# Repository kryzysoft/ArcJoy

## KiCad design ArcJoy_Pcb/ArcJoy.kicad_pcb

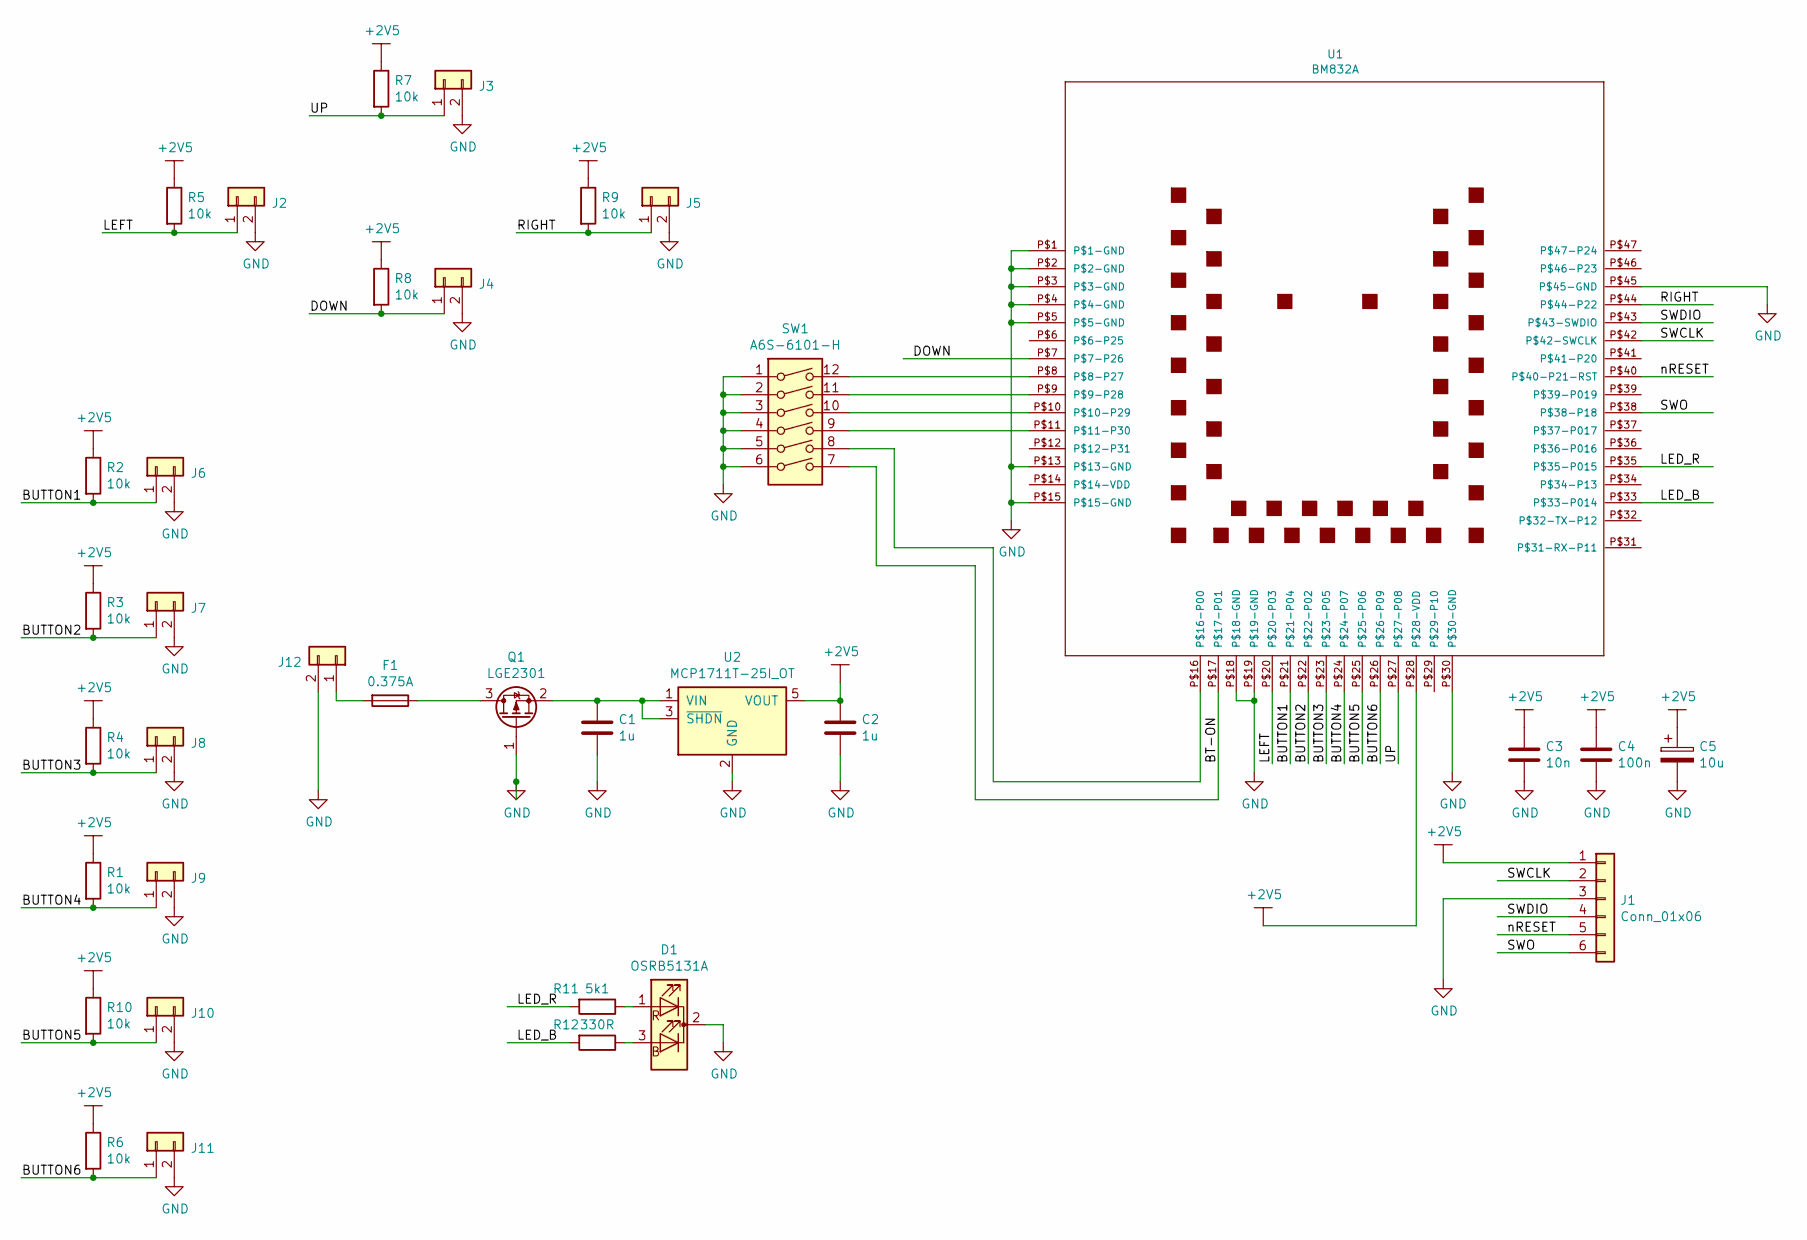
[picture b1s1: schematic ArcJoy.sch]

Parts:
C1, C2: 1u; C_1206_3216Metric
C3: 10n; C_1206_3216Metric
C4: 100n; C_1206_3216Metric
C5: 10u; CP_EIA-6032-28_Kemet-C
D1: OSRB5131A; LED_D5.0mm-3
F1: 0.375A; Fuse_2.6x6.1
J1: Conn_01x06; PinHeader_1x06_P2.54mm_Vertical
J2, J3, J4, J5: Conn_01x02; PinHeader_1x02_P2.54mm_Vertical
J6, J7, J8, J9, J10, J11, J12: Conn_01x02; NINIGI_TB-3.5-P-2P_BL
Q1: LGE2301; SOT-23
R1, R2, R3, R4, R5, R6, R7, R8, R9, R10: 10k; R_1206_3216Metric
R11: 5k1_1206_1%; R_1206_3216Metric
R12: 330R_1206_1%; R_1206_3216Metric
SW1: A6S-6101-H; SW_DIP_SPSTx06_Slide_Omron_A6S-610x_W8.9mm_P2.54mm
U1: BM832A; BM832-1-BM832
U2: MCP1711T-25I_OT; SOT-23-5

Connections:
+2V5: C2.1, C3.1, C4.1, C5.1, J1.1, R1.1, R2.1, R3.1, R4.1, R5.1, R6.1, R7.1, R8.1, R9.1, R10.1, U1.P$28 (P$28-VDD), U2.5 (VOUT)
/BT-ON: SW1.7, U1.P$17 (P$17-P01)
/BUTTON1: J6.1, R2.2, U1.P$21 (P$21-P04)
/BUTTON2: J7.1, R3.2, U1.P$22 (P$22-P02)
/BUTTON3: J8.1, R4.2, U1.P$23 (P$23-P05)
/BUTTON4: J9.1, R1.2, U1.P$24 (P$24-P07)
/BUTTON5: J10.1, R10.2, U1.P$25 (P$25-P06)
/BUTTON6: J11.1, R6.2, U1.P$26 (P$26-P09)
/DOWN: J4.1, R8.2, U1.P$7 (P$7-P26)
/LED_B: R12.2, U1.P$33 (P$33-P014)
/LED_R: R11.2, U1.P$35 (P$35-P015)
/LEFT: J2.1, R5.2, U1.P$20 (P$20-P03)
/RIGHT: J5.1, R9.2, U1.P$44 (P$44-P22)
/SWCLK: J1.2, U1.P$42 (P$42-SWCLK)
/SWDIO: J1.4, U1.P$43 (P$43-SWDIO)
/SWO: J1.6, U1.P$38 (P$38-P18)
/UP: J3.1, R7.2, U1.P$27 (P$27-P08)
/nRESET: J1.5, U1.P$40 (P$40-P21-RST)
GND: C1.2, C2.2, C3.2, C4.2, C5.2, D1.2 (K), J1.3, J2.2, J3.2, J4.2, J5.2, J6.2, J7.2, J8.2, J9.2, J10.2, J11.2, J12.2, Q1.1 (G), SW1.1, SW1.2, SW1.3, SW1.4, SW1.5, SW1.6, U1.P$1 (P$1-GND), U1.P$2 (P$2-GND), U1.P$3 (P$3-GND), U1.P$4 (P$4-GND), U1.P$5 (P$5-GND), U1.P$13 (P$13-GND), U1.P$15 (P$15-GND), U1.P$18 (P$18-GND), U1.P$19 (P$19-GND), U1.P$30 (P$30-GND), U1.P$45 (P$45-GND), U2.2 (GND)
unnamed: C1.1, Q1.2 (S), U2.1 (VIN), U2.3 (~SHDN)
unnamed: D1.1 (RA), R11.1
unnamed: D1.3 (BA), R12.1
unnamed: F1.1, Q1.3 (D)
unnamed: F1.2, J12.1
unnamed: SW1.8, U1.P$16 (P$16-P00)
unnamed: SW1.9, U1.P$11 (P$11-P30)
unnamed: SW1.10, U1.P$10 (P$10-P29)
unnamed: SW1.11, U1.P$9 (P$9-P28)
unnamed: SW1.12, U1.P$8 (P$8-P27)

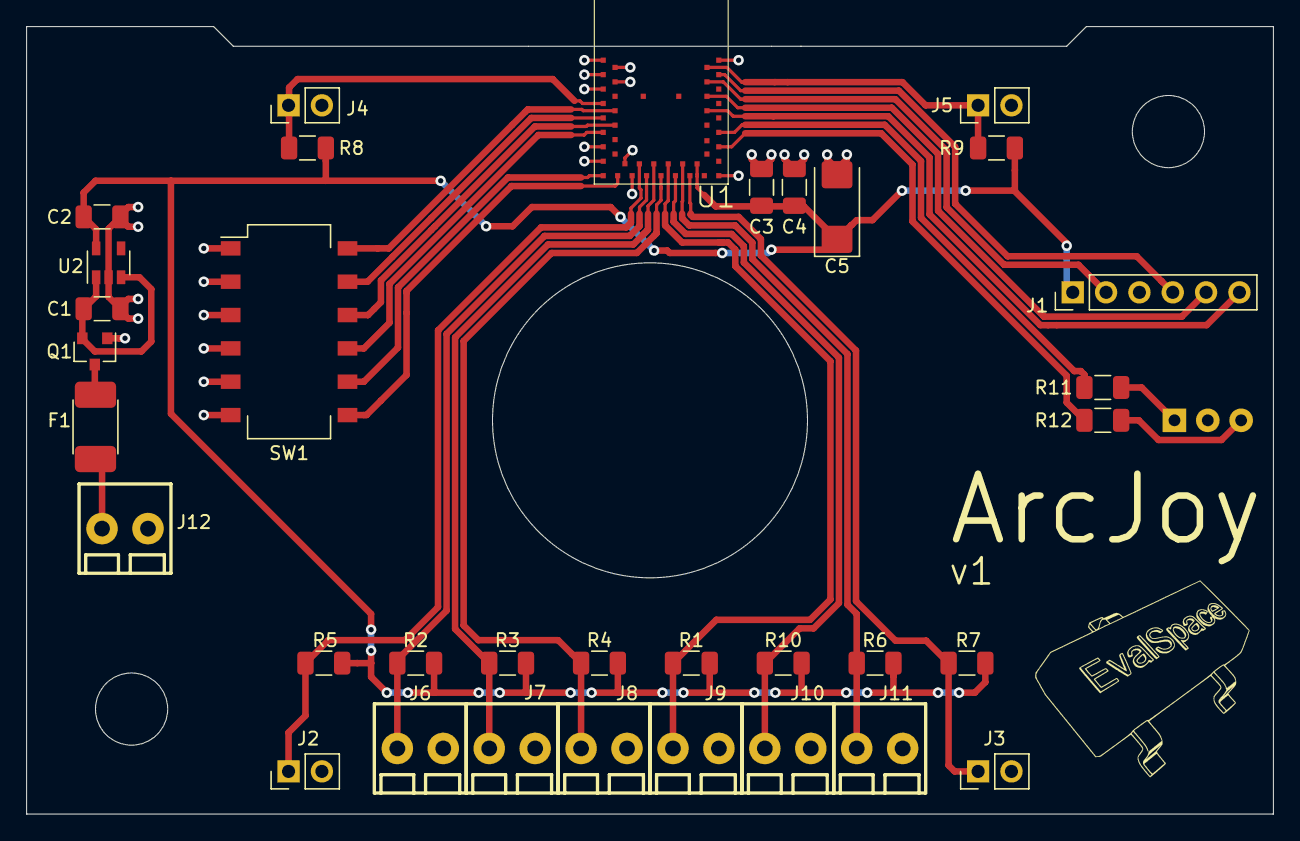
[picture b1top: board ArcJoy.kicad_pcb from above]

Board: 2 copper layers, 95.0 x 60.0 mm, 35 parts (1 on the bottom side), 29 nets.

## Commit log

2019-05-06 1st commit
2019-05-07 Enhanced Shock Burst added.
2019-05-08 Log by RTT
2019-06-29 New SDK
2019-06-30 LEDs and dipswitch managing.
2019-07-02 ArcBase project added
2019-07-02 App moved to joyApp.cpp file
2019-07-03 Timer tests
2019-07-06 Before new ArcBase project
2019-07-06 .gitignore modified
2019-07-06 USB project copied from SDK
2019-07-06 ESP working
2019-07-06 Working as mouse.
2019-07-07 Base works as a joystick
2019-07-07 BGA Soldering test - toggling all pins
2019-07-07 Pullup and release time
2019-07-08 LED test
2019-07-08 Wire lengths
2019-07-08 Pull up, release times
2019-07-08 Wires
2019-07-09 Conversion to c++
2019-07-10 Joy and radio in IHal
2019-07-10 emSession removed. Unused functions removed.
2019-07-11 Gpio & Rtc alarm in IHal
2019-07-12 Low power modes in IHal
2019-07-12 Dependency removed
2019-07-12 Unused files removed
2019-07-14 COnversion started
2019-07-15 Some changes
2019-07-15 2 joysticks not working yet
2019-07-15 Mouse & keyboard
2019-07-15 2 joysticks hid working
2019-07-16 Joy number selectable by dipswitch
2019-07-17 ArcBase conversion to CPP
2019-07-20 Converted to cpp
2019-07-20 LEDs working
2019-08-04 ArcBase case
2019-08-06 RTT Test
2019-08-07 Repeat until success
2019-08-11 ArcJoy.pdf added
2019-08-13 Bom updated
2019-08-14 Case updated
2019-08-15 Case updated again
2019-08-16 Net +2V2 changed to +2V5
2019-08-18 Retransmit count increased to 40 (10 ms)
2019-08-18 Communication effectiveness increased
2019-08-21 Rtt working
2019-08-23 RTT log working
2019-08-24 Refactoring done
2019-08-26 Periodic event interface
2019-08-28 Debouncer and switch controller.
2019-08-29 Sleep management
2019-08-29 Debouncer simplified
2019-08-29 Debouncer simplified 2
2019-08-30 DelayedEventHandler
2019-08-31 IHal and nRF_Hal updates
2019-08-31 IHal updates
2019-08-31 Cleanup
2019-08-31 Wake up info
2019-08-31 Hal updates
2019-08-31 NrfGpioInputIrq.cpp removed from project
2019-09-04 Warnings and Errors
2019-09-06 IHal moved outside
2019-09-06 IHal added to ArcJoy
2019-09-06 IHal removed from ArcBase
2019-09-06 src/IHal problem
2019-09-06 IHal submodule added to ArcBase
2019-09-06 ArcBase project updated
2019-09-06 Submodule changes
2019-09-06 Submodule update
2019-09-06 IHal in ArcJoy updated
2019-09-06 IHal updated
2019-09-06 Refactoring
2019-09-08 Poprawka zaciągnięta
2019-09-08 Poprawka
2019-09-08 Poprawka usunieta
2019-09-08 nRF_Hal separated from IHal
2019-09-08 nRF_Hal added
2019-09-08 File paths updated in project
2019-09-08 IHal updated done
